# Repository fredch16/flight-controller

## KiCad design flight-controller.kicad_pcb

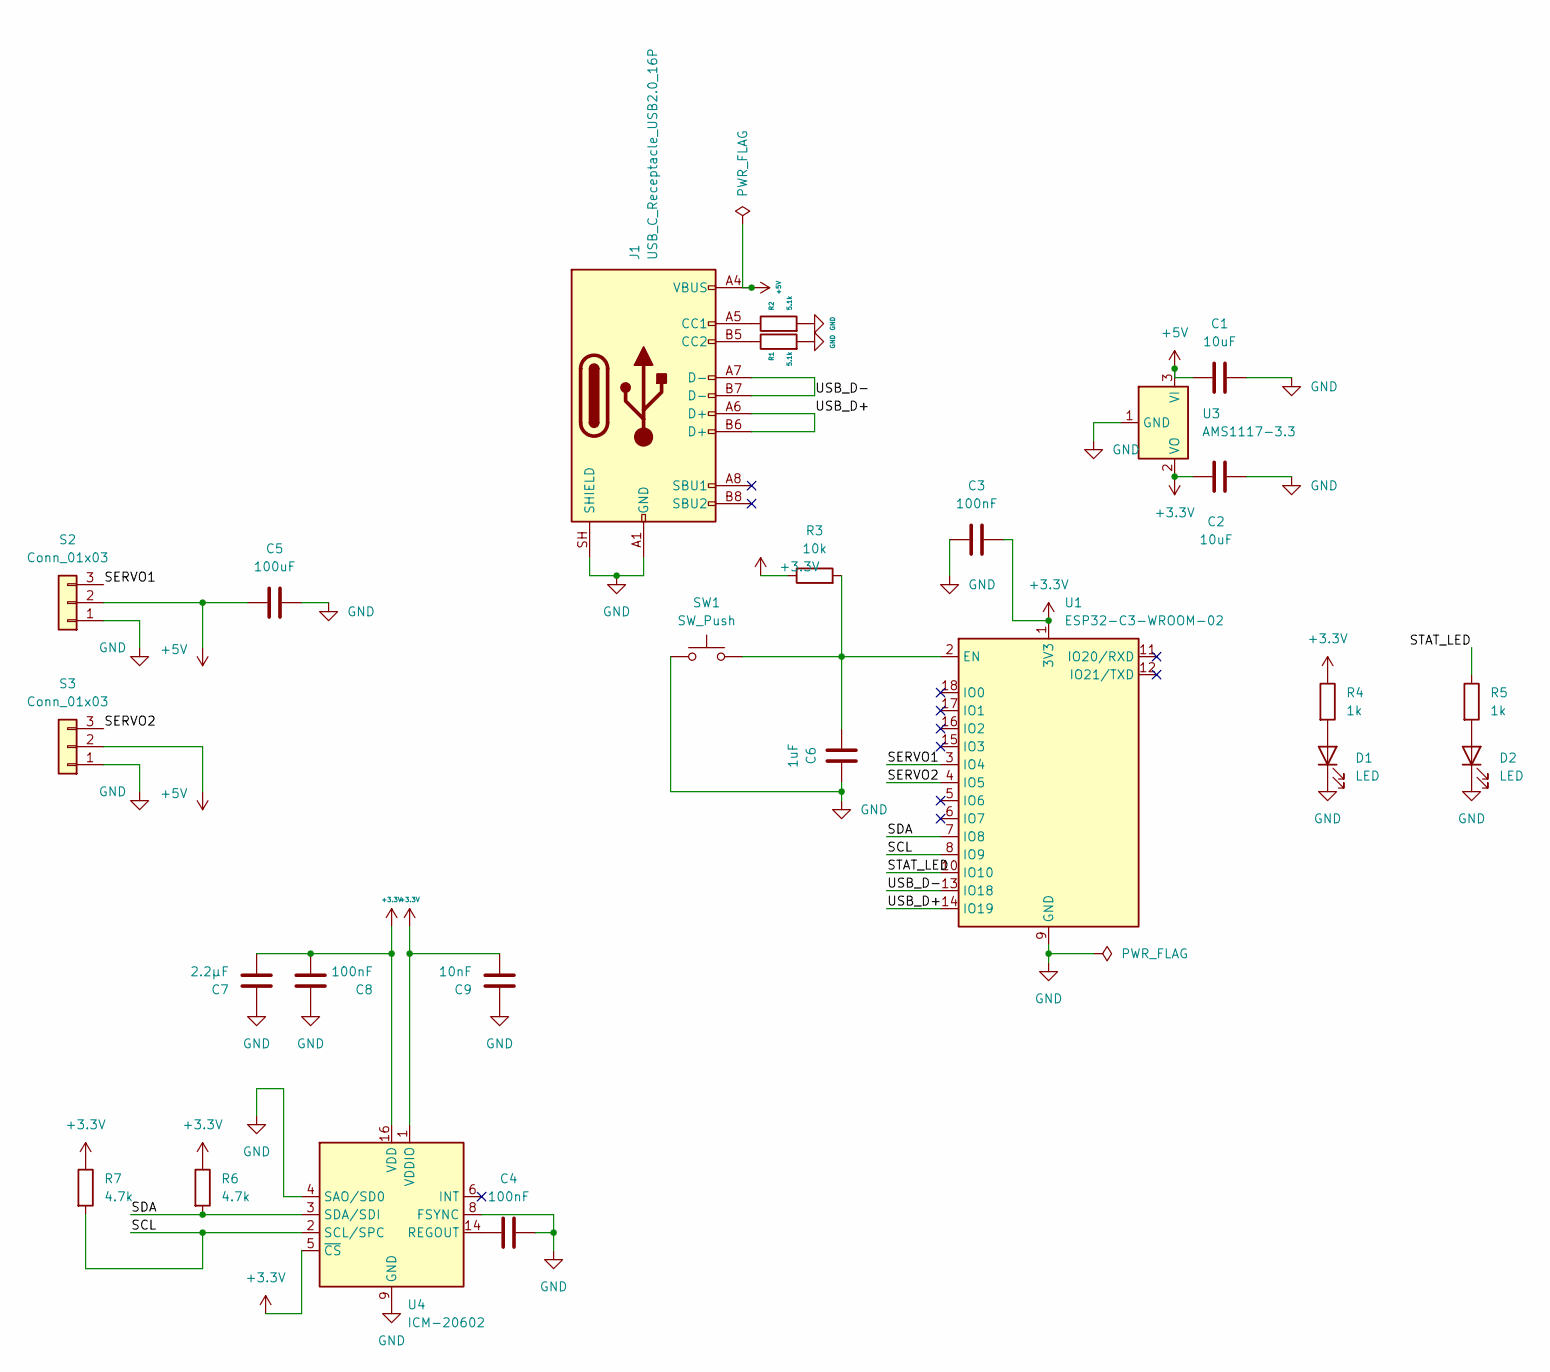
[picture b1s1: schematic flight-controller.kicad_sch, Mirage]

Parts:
C1, C2: 10uF; C_0805_2012Metric
C3, C4, C8: 100nF; C_0805_2012Metric
C5: 100uF; C_0805_2012Metric
C6: 1uF; C_0805_2012Metric
C7: 2.2µF; C_0805_2012Metric
C9: 10nF; C_0805_2012Metric
D1, D2: LED; LED_0805_2012Metric
J1: USB_C_Receptacle_USB2.0_16P; USB_C_Receptacle_HRO_TYPE-C-31-M-12
R1, R2: 5.1k; R_0805_2012Metric
R3: 10k; R_0805_2012Metric
R4, R5: 1k; R_0805_2012Metric
R6, R7: 4.7k; R_0805_2012Metric
S2, S3: Conn_01x03; FanPinHeader_1x03_P2.54mm_Vertical
SW1: SW_Push; SW_SPST_PTS647_Sx38
U1: ESP32-C3-WROOM-02
U3: AMS1117-3.3; SOT-223-3_TabPin2
U4: ICM-20602; LGA-16_3x3mm_P0.5mm_LayoutBorder3x5y

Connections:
+3.3V: C2.1, C3.2, C7.2, C8.2, C9.2, R3.1, R4.1, R6.1, R7.1, U1.1 (3V3), U3.2 (VO), U4.1 (VDDIO), U4.5 (~CS), U4.16 (VDD)
+5V: C1.1, C5.1, J1.A4 (VBUS), J1.A9 (VBUS), J1.B4 (VBUS), J1.B9 (VBUS), S2.2, S3.2, U3.3 (VI)
/SCL: R7.2, U1.8 (IO9), U4.2 (SCL/SPC)
/SDA: R6.2, U1.7 (IO8), U4.3 (SDA/SDI)
/SERVO1: S2.3, U1.3 (IO4)
/SERVO2: S3.3, U1.4 (IO5)
/STAT_LED: R5.1, U1.10 (IO10)
/USB_D+: J1.A6 (D+), J1.B6 (D+), U1.14 (IO19)
/USB_D-: J1.A7 (D-), J1.B7 (D-), U1.13 (IO18)
GND: C1.2, C2.2, C3.1, C4.1, C5.2, C6.2, C7.1, C8.1, C9.1, D1.1 (K), D2.1 (K), J1.A1 (GND), J1.A12 (GND), J1.B1 (GND), J1.B12 (GND), J1.SH (SHIELD), R1.2, R2.2, S2.1, S3.1, SW1.1, U1.9 (GND), U1.19 (GND), U3.1 (GND), U4.4 (SAO/SD0), U4.8 (FSYNC), U4.9 (GND), U4.10 (GND), U4.11 (GND), U4.12 (GND), U4.13 (GND), U4.15 (GND); also elsewhere on the board
unnamed 10: D1.2 (A), R4.2; also elsewhere on the board
unnamed 11: D2.2 (A), R5.2; also elsewhere on the board
unnamed: J1.A5 (CC1), R2.1
unnamed: J1.B5 (CC2), R1.1
unnamed: C6.1, R3.2, SW1.2, U1.2 (EN)
unnamed: C4.2, U4.14 (REGOUT)

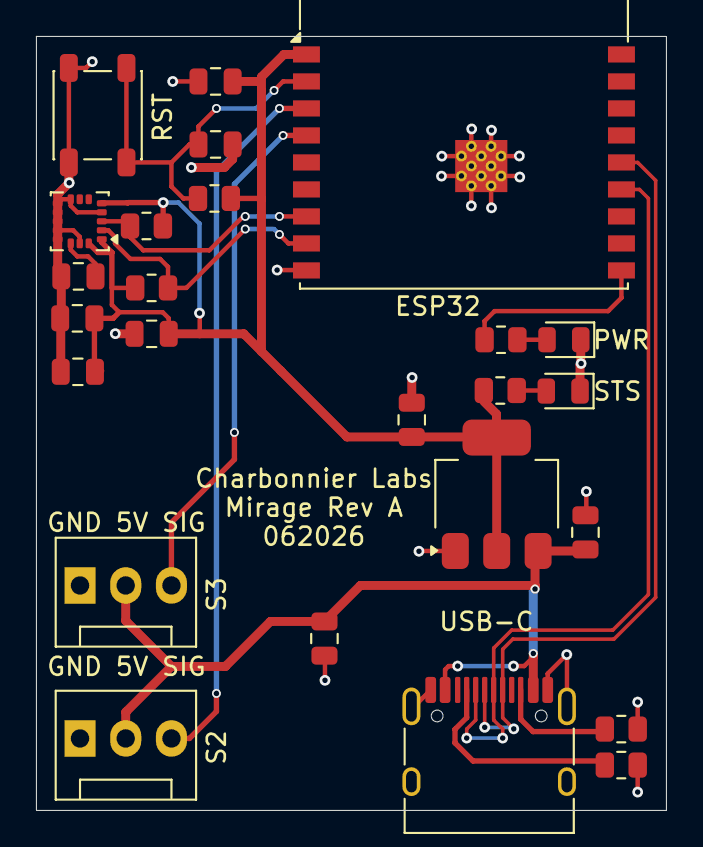
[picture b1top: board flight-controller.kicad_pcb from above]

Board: 2 copper layers, 35.0 x 43.0 mm, 25 parts (0 on the bottom side), 16 nets.

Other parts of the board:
PWR: LED; LED_0805_2012Metric
STS: LED; LED_0805_2012Metric

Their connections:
GND: PWR.1 (K), STS.1 (K); also elsewhere on the board
unnamed 10: STS.2 (A); also elsewhere on the board
unnamed 11: PWR.2 (A); also elsewhere on the board

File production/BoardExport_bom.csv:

Designator,Footprint,Quantity,Value,LCSC Part #
"C1, C2",0805,2,10uF,
"C3, C4",0805,2,100nF,
C5,0805,1,100uF,
C6,0805,1,1uF,
J1,USB_C_Receptacle_HRO_TYPE-C-31-M-12,1,USB_C_Receptacle_USB2.0_16P,
"R1, R2",0805,2,5.1k,
R3,0805,1,10k,
"SERVO1, SERVO2",FanPinHeader_1x03_P2.54mm_Vertical,2,Conn_01x03,
SW1,SW_SPST_PTS647_Sx38,1,SW_Push,
U1,ESP32-C3-WROOM-02,1,ESP32-C3-WROOM-02,
U2,InvenSense_QFN-24_4x4mm_P0.5mm,1,MPU-6050,
U3,SOT-223-3_TabPin2,1,AMS1117-3.3,

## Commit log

2026-06-23 Added files from kicad
2026-06-23 NEW - Implemented Ground plane on B.Cu to join all GNDs together. FIX - Rotated LDO to reduce length of 5v and 3.3v connection FIX - Moved C1 to reduce length of 5v connection NEW - All GNDs connecte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
2026-06-24 Modified some routing to resolve some clearance issues
2026-06-24 - Redid all the traces from scratch with a much clearer design plan - Much cleaner paths, large and thick powerlines, thinner and more direct signal lines Ground plate works better now
2026-06-24 - Reduced height of the board to have the antenna hang off completely instead of being on top of any plate
2026-06-24 Added Silkscreen annotations
2026-06-24 Adjusted version silkscreen
2026-06-25 Fixing version control?
2026-06-26 Improvements to schematics and PCB design. - GND always points down - Power always points up - Adjusted powerlines
2026-06-26 Restructued Layout slightly and added new BOM
2026-06-28 Added a Power LED indicator Added a Status LED indicator Replaced MPU6050 with cheaper and more modern ICM-20602
2026-06-28 Added pull up resistors to SDA and SCL pins
2026-06-28 Redone the layout of the PCB to incorporate the Power LED and Status LED Also removed MPU6050 and replaced with IMC 20602 and relevant capacitors Added 2 pull up resistors to SCL and SDA lines
